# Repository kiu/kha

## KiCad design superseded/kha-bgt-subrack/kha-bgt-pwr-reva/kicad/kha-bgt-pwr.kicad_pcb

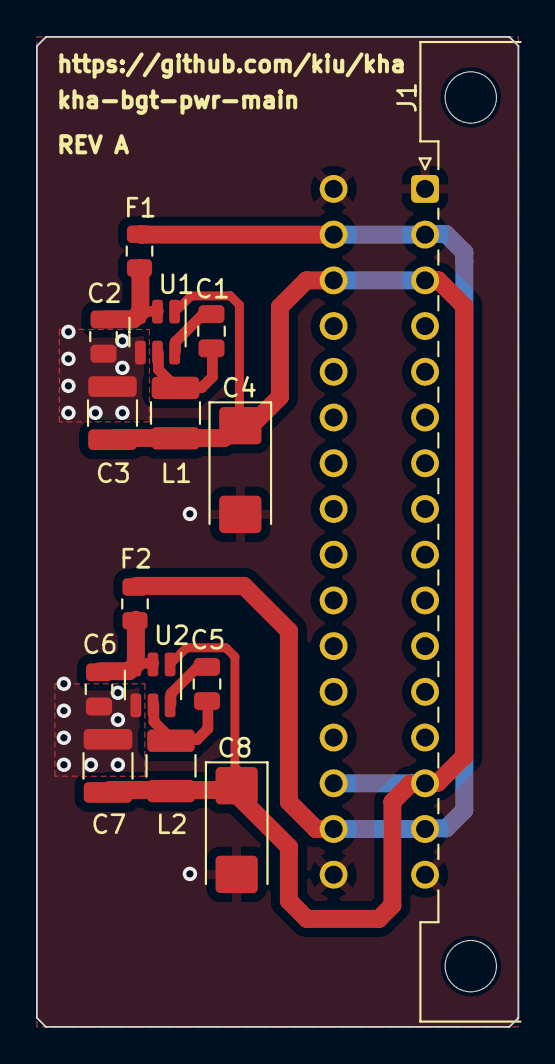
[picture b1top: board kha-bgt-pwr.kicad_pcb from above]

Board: 2 copper layers, 26.8 x 55.0 mm, 15 parts (0 on the bottom side), 9 nets.

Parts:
C1, C2, C5, C6: C; C_0805_2012Metric
C3, C7: C; C_1210_3225Metric
C4, C8: C_Polarized; CP_EIA-6032-28_Kemet-C
F1, F2: Polyfuse; Fuse_0805_2012Metric
J1: DIN41612_02x16_AC; DIN41612_C2_2x16_Male_Horizontal_THT
L1, L2: L; L_1210_3225Metric
U1, U2: AP63205WU; TSOT-23-6

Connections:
+5V: C3.1, C4.1, C7.1, C8.1, J1.a3, J1.a14, J1.c3, J1.c14, L1.2, L2.2, U1.1 (FB), U2.1 (FB)
+12V: F1.2, F2.2, J1.a2, J1.a15, J1.c2, J1.c15
GND: C2.1, C3.2, C4.2, C6.1, C7.2, C8.2, J1.a1, J1.a16, J1.c1, J1.c16, U1.4 (GND), U2.4 (GND)
unnamed: C1.2, U1.6 (BST)
unnamed: C2.2, F1.1, U1.2 (EN), U1.3 (IN)
unnamed: C1.1, L1.1, U1.5 (SW)
unnamed: C5.2, U2.6 (BST)
unnamed: C6.2, F2.1, U2.2 (EN), U2.3 (IN)
unnamed: C5.1, L2.1, U2.5 (SW)

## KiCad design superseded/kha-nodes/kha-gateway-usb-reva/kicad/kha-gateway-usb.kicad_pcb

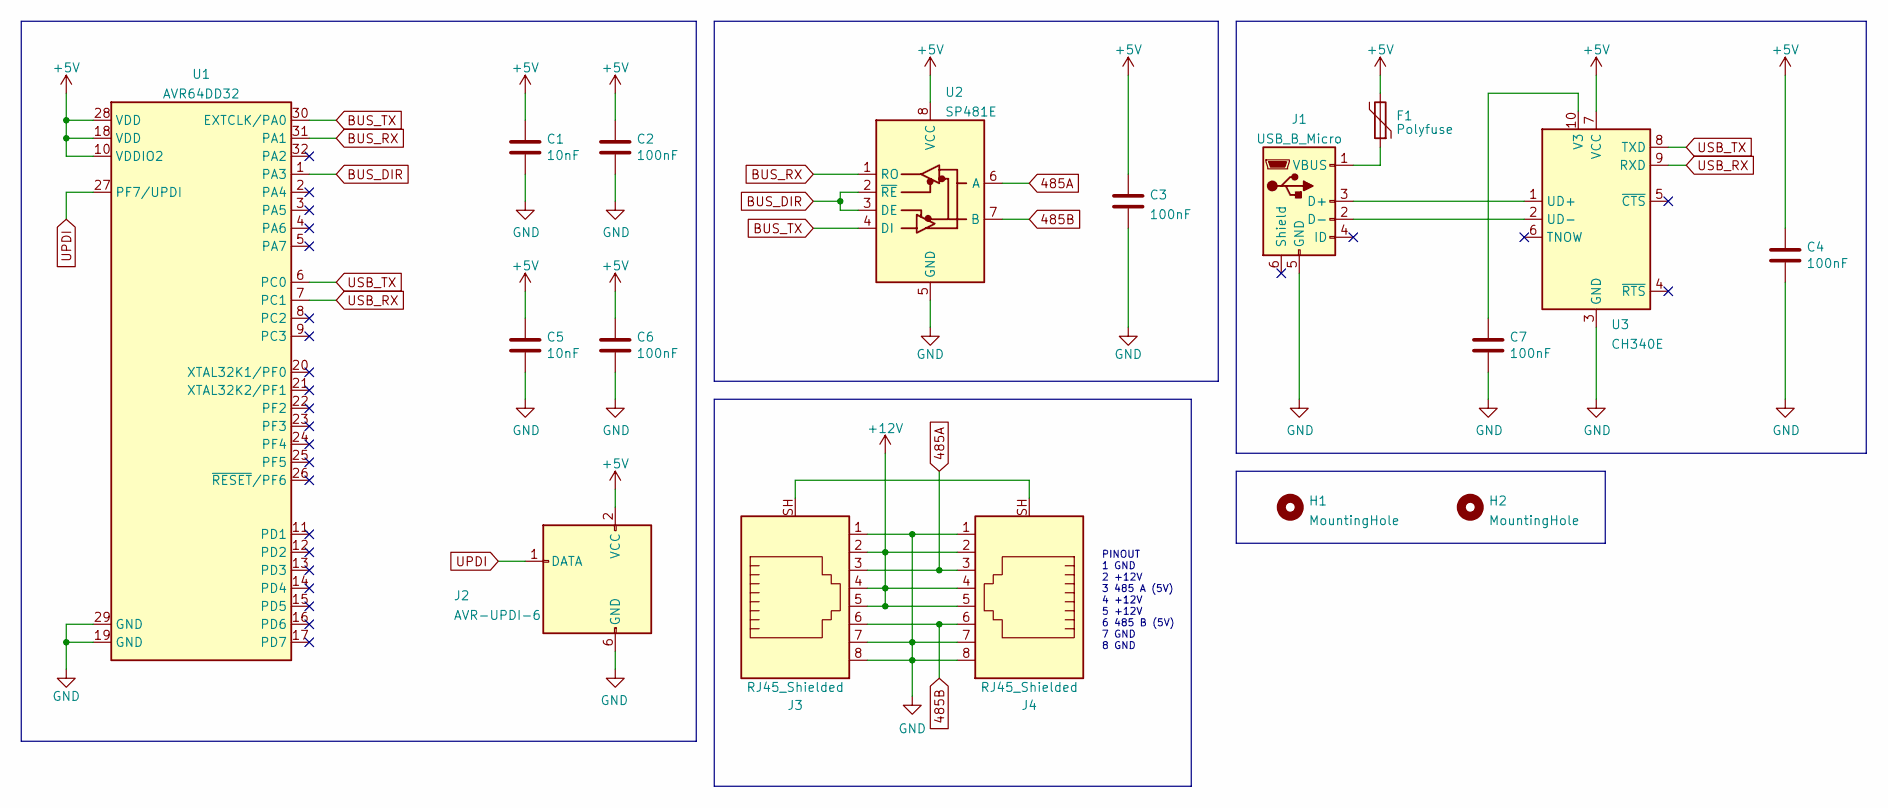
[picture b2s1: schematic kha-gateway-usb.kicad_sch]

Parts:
C1, C5: 10nF; C_0805_2012Metric
C2, C3, C4, C6, C7: 100nF; C_0805_2012Metric
F1: Polyfuse; Fuse_0805_2012Metric
H1, H2: MountingHole; MountingHole_3.2mm_M3_DIN965
J1: USB_B_Micro; GCT-USB3076-30-A
J2: AVR-UPDI-6; eAVR6-UPDI-F
J3, J4: RJ45_Shielded; GDLX-S-88K
U1: AVR64DD32; TQFP-32_7x7mm_P0.8mm
U2: SP481E; SOIC-8_3.9x4.9mm_P1.27mm
U3: CH340E; MSOP-10_3x3mm_P0.5mm

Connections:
485A: J3.3, J4.3, U2.6 (A)
485B: J3.6, J4.6, U2.7 (B)
+5V: C1.1, C2.1, C3.1, C4.1, C5.1, C6.1, F1.2, J2.2 (VCC), U1.10 (VDDIO2), U1.18 (VDD), U1.28 (VDD), U2.8 (VCC), U3.7 (VCC)
+12V: J3.2, J3.4, J3.5, J4.2, J4.4, J4.5
BUS_DIR: U1.1 (PA3), U2.2 (~RE), U2.3 (DE)
BUS_RX: U1.31 (PA1), U2.1 (RO)
BUS_TX: U1.30 (EXTCLK/PA0), U2.4 (DI)
GND: C1.2, C2.2, C3.2, C4.2, C5.2, C6.2, C7.2, J1.5 (GND), J2.6 (GND), J3.1, J3.7, J3.8, J4.1, J4.7, J4.8, U1.19 (GND), U1.29 (GND), U2.5 (GND), U3.3 (GND)
unnamed: J1.3 (D+), U3.1 (UD+)
unnamed: J1.2 (D-), U3.2 (UD-)
unnamed: F1.1, J1.1 (VBUS)
unnamed: J3.SH, J4.SH
unnamed: C7.1, U3.10 (V3)
UPDI: J2.1 (DATA), U1.27 (PF7/UPDI)
USB_RX: U1.7 (PC1), U3.9 (RXD)
USB_TX: U1.6 (PC0), U3.8 (TXD)

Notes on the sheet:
PINOUT 1 GND 2 +12V 3 485 A (5V) 4 +12V 5 +12V 6 485 B (5V) 7 GND 8 GND

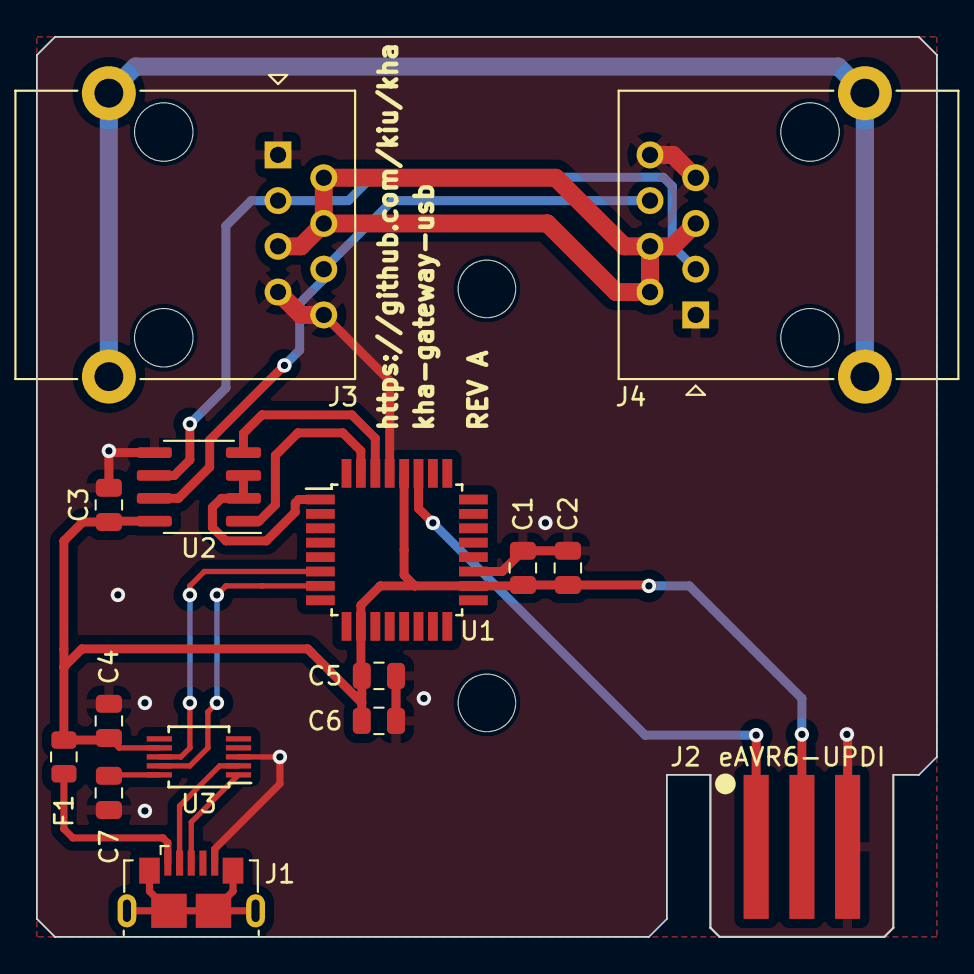
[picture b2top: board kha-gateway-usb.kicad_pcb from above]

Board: 2 copper layers, 50.0 x 50.0 mm, 17 parts (0 on the bottom side), 16 nets.

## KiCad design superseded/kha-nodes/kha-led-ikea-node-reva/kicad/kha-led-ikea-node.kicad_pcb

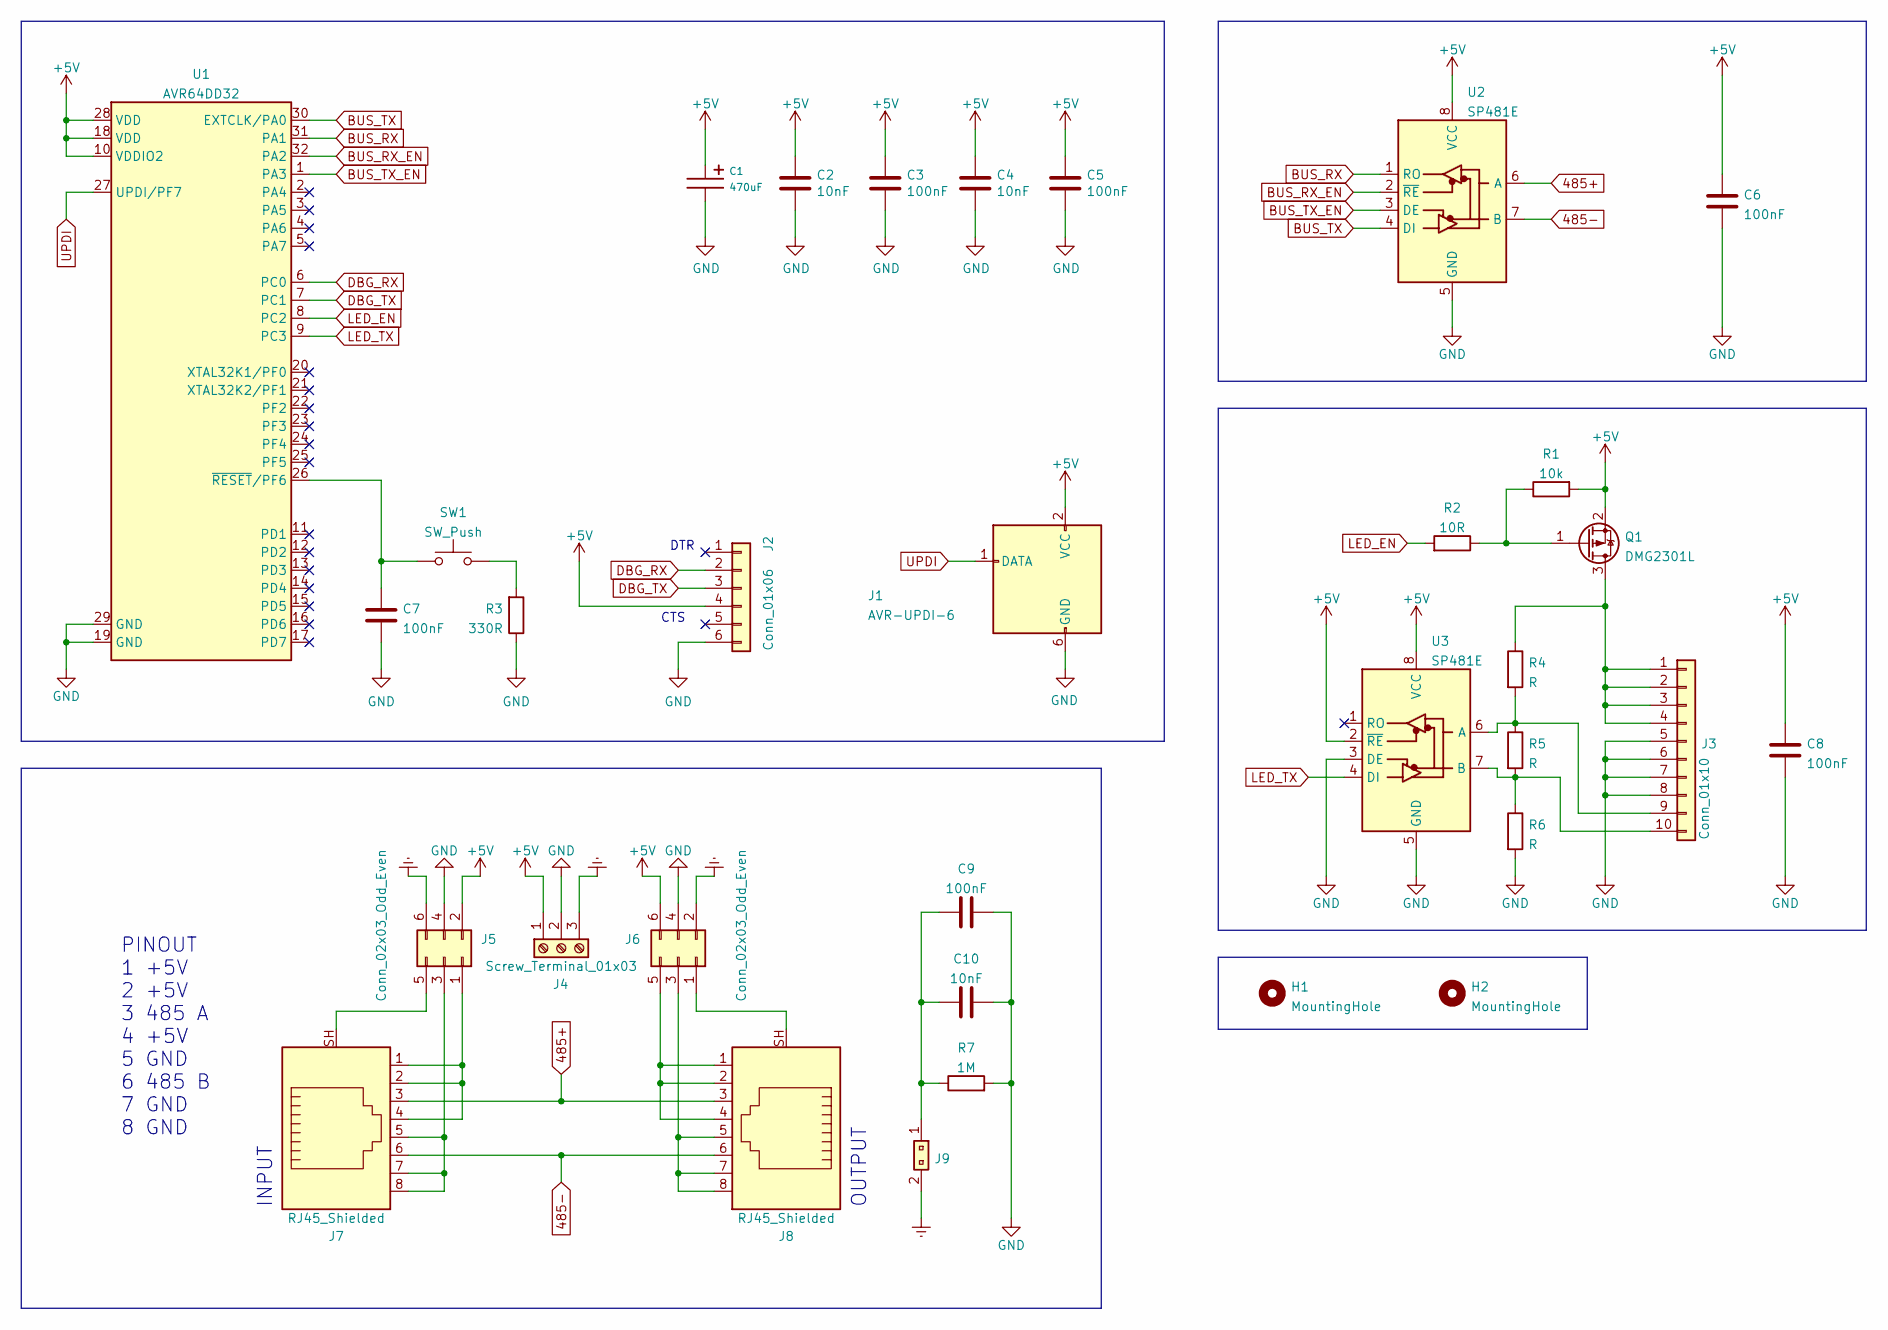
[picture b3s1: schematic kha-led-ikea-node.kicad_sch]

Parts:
C1: 470uF; CP_Elec_8x10
C2, C4, C10: 10nF; C_0805_2012Metric
C3, C5, C6, C7, C8, C9: 100nF; C_0805_2012Metric
H1, H2: MountingHole; MountingHole_3.2mm_M3
J1: AVR-UPDI-6; eAVR6-UPDI-F
J2: Conn_01x06; PinSocket_1x06_P2.54mm_Vertical
J3: Conn_01x10; IDC-Header_2x05_P2.54mm_Vertical
J4: Screw_Terminal_01x03; TerminalBlock_RND_205-00233_1x03_P5.08mm_Horizontal
J5, J6: Conn_02x03_Odd_Even; PinHeader_2x03_P2.54mm_Vertical
J7, J8: RJ45_Shielded; GDLX-S-88K
J9: 1x02_Jumper; PinHeader_1x02_P2.54mm_Vertical
Q1: DMG2301L; SOT-23
R1: 10k; R_0805_2012Metric
R2: 10R; R_0805_2012Metric
R3: 330R; R_0805_2012Metric
R4, R5, R6: R; R_0805_2012Metric
R7: 1M; R_0805_2012Metric
SW1: SW_Push; SW_Push_1P1T_NO_6x6mm_H9.5mm
U1: AVR64DD32; TQFP-32_7x7mm_P0.8mm
U2, U3: SP481E; SOIC-8_3.9x4.9mm_P1.27mm

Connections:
485+: J7.3, J8.3, U2.6 (A)
485-: J7.6, J8.6, U2.7 (B)
+5V: C1.1, C2.1, C3.1, C4.1, C5.1, C6.1, C8.1, J1.2 (VCC), J2.4, J4.1, J5.2, J6.6, Q1.2 (S), R1.2, U1.10 (VDDIO2), U1.18 (VDD), U1.28 (VDD), U2.8 (VCC), U3.2 (~RE), U3.8 (VCC)
BUS_RX: U1.31 (PA1), U2.1 (RO)
BUS_RX_EN: U1.32 (PA2), U2.2 (~RE)
BUS_TX: U1.30 (EXTCLK/PA0), U2.4 (DI)
BUS_TX_EN: U1.1 (PA3), U2.3 (DE)
DBG_RX: J2.2, U1.6 (PC0)
DBG_TX: J2.3, U1.7 (PC1)
Earth: J4.3, J5.6, J6.2, J9.2
GND: C1.2, C2.2, C3.2, C4.2, C5.2, C6.2, C7.2, C8.2, C9.2, C10.2, J1.6 (GND), J2.6, J3.5, J3.6, J3.7, J3.8, J4.2, J5.4, J6.4, R3.1, R6.2, R7.2, U1.19 (GND), U1.29 (GND), U2.5 (GND), U3.3 (DE), U3.5 (GND)
LED_EN: R2.2, U1.8 (PC2)
LED_TX: U1.9 (PC3), U3.4 (DI)
unnamed: C7.1, SW1.1, U1.26 (~RESET/PF6)
unnamed: C9.1, C10.1, J9.1, R7.1
unnamed: J3.1, J3.2, J3.3, J3.4, Q1.3 (D), R4.1
unnamed: J3.9, R4.2, R5.1, U3.6 (A)
unnamed: J5.1, J7.1, J7.2, J7.4
unnamed: J5.3, J7.5, J7.7, J7.8
unnamed: J5.5, J7.SH
unnamed: J6.1, J8.SH
unnamed: J6.3, J8.5, J8.7, J8.8
unnamed: J6.5, J8.1, J8.2, J8.4
unnamed: Q1.1 (G), R1.1, R2.1
unnamed: R3.2, SW1.2
unnamed: J3.10, R5.2, R6.1, U3.7 (B)
UPDI: J1.1 (DATA), U1.27 (UPDI/PF7)

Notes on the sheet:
CTS
PINOUT 1 +5V 2 +5V 3 485 A 4 +5V 5 GND 6 485 B 7 GND 8 GND
OUTPUT
INPUT
DTR

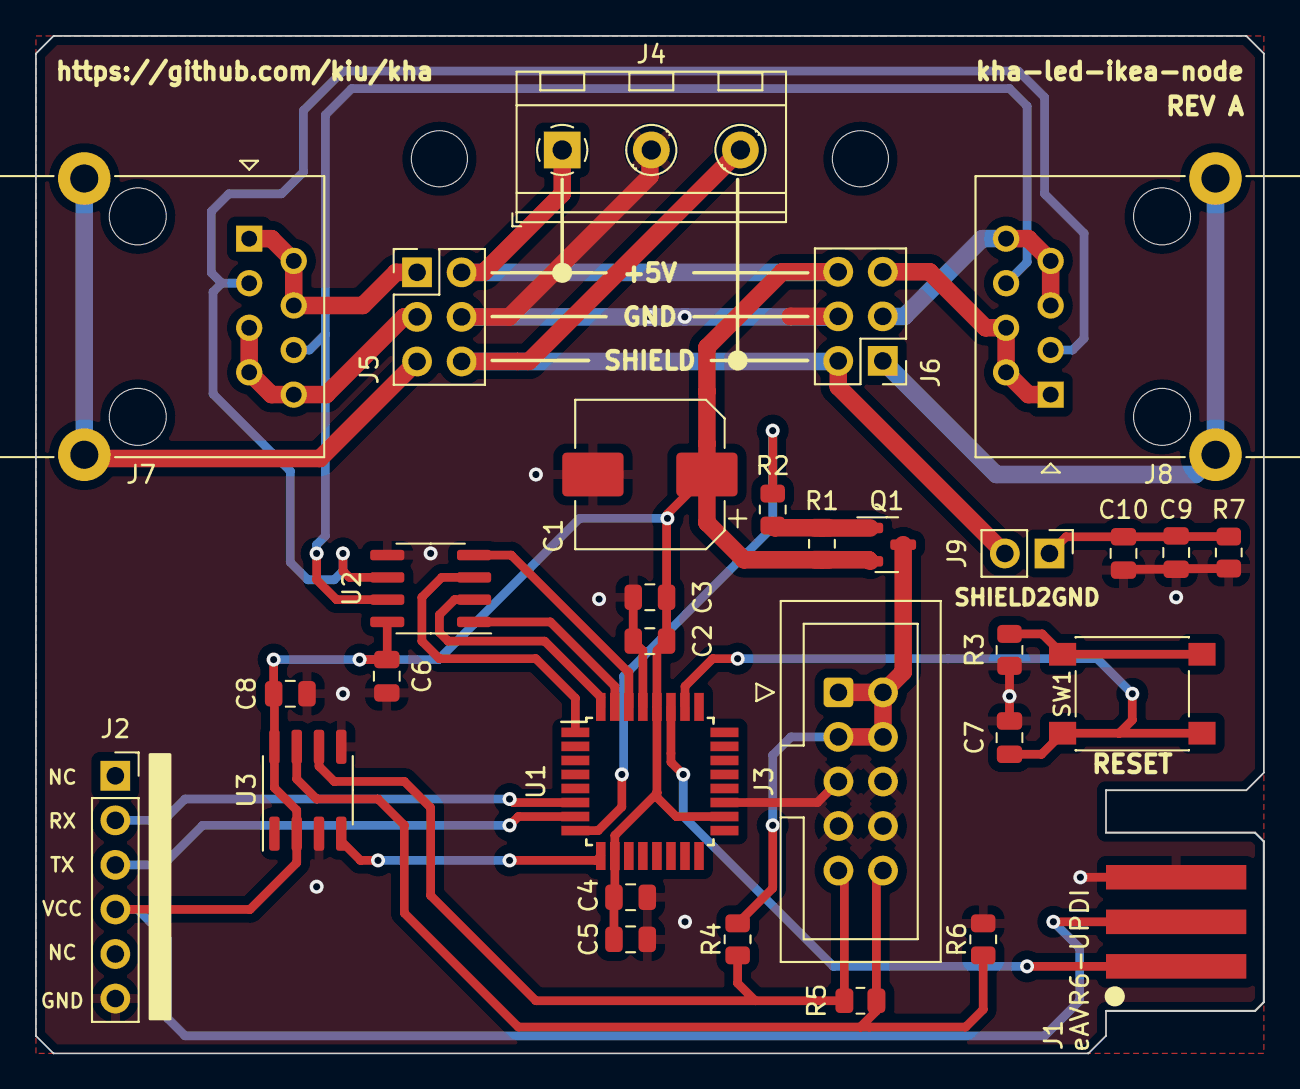
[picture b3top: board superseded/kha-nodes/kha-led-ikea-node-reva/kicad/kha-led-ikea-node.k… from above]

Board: 2 copper layers, 70.0 x 58.0 mm, 33 parts (0 on the bottom side), 27 nets.

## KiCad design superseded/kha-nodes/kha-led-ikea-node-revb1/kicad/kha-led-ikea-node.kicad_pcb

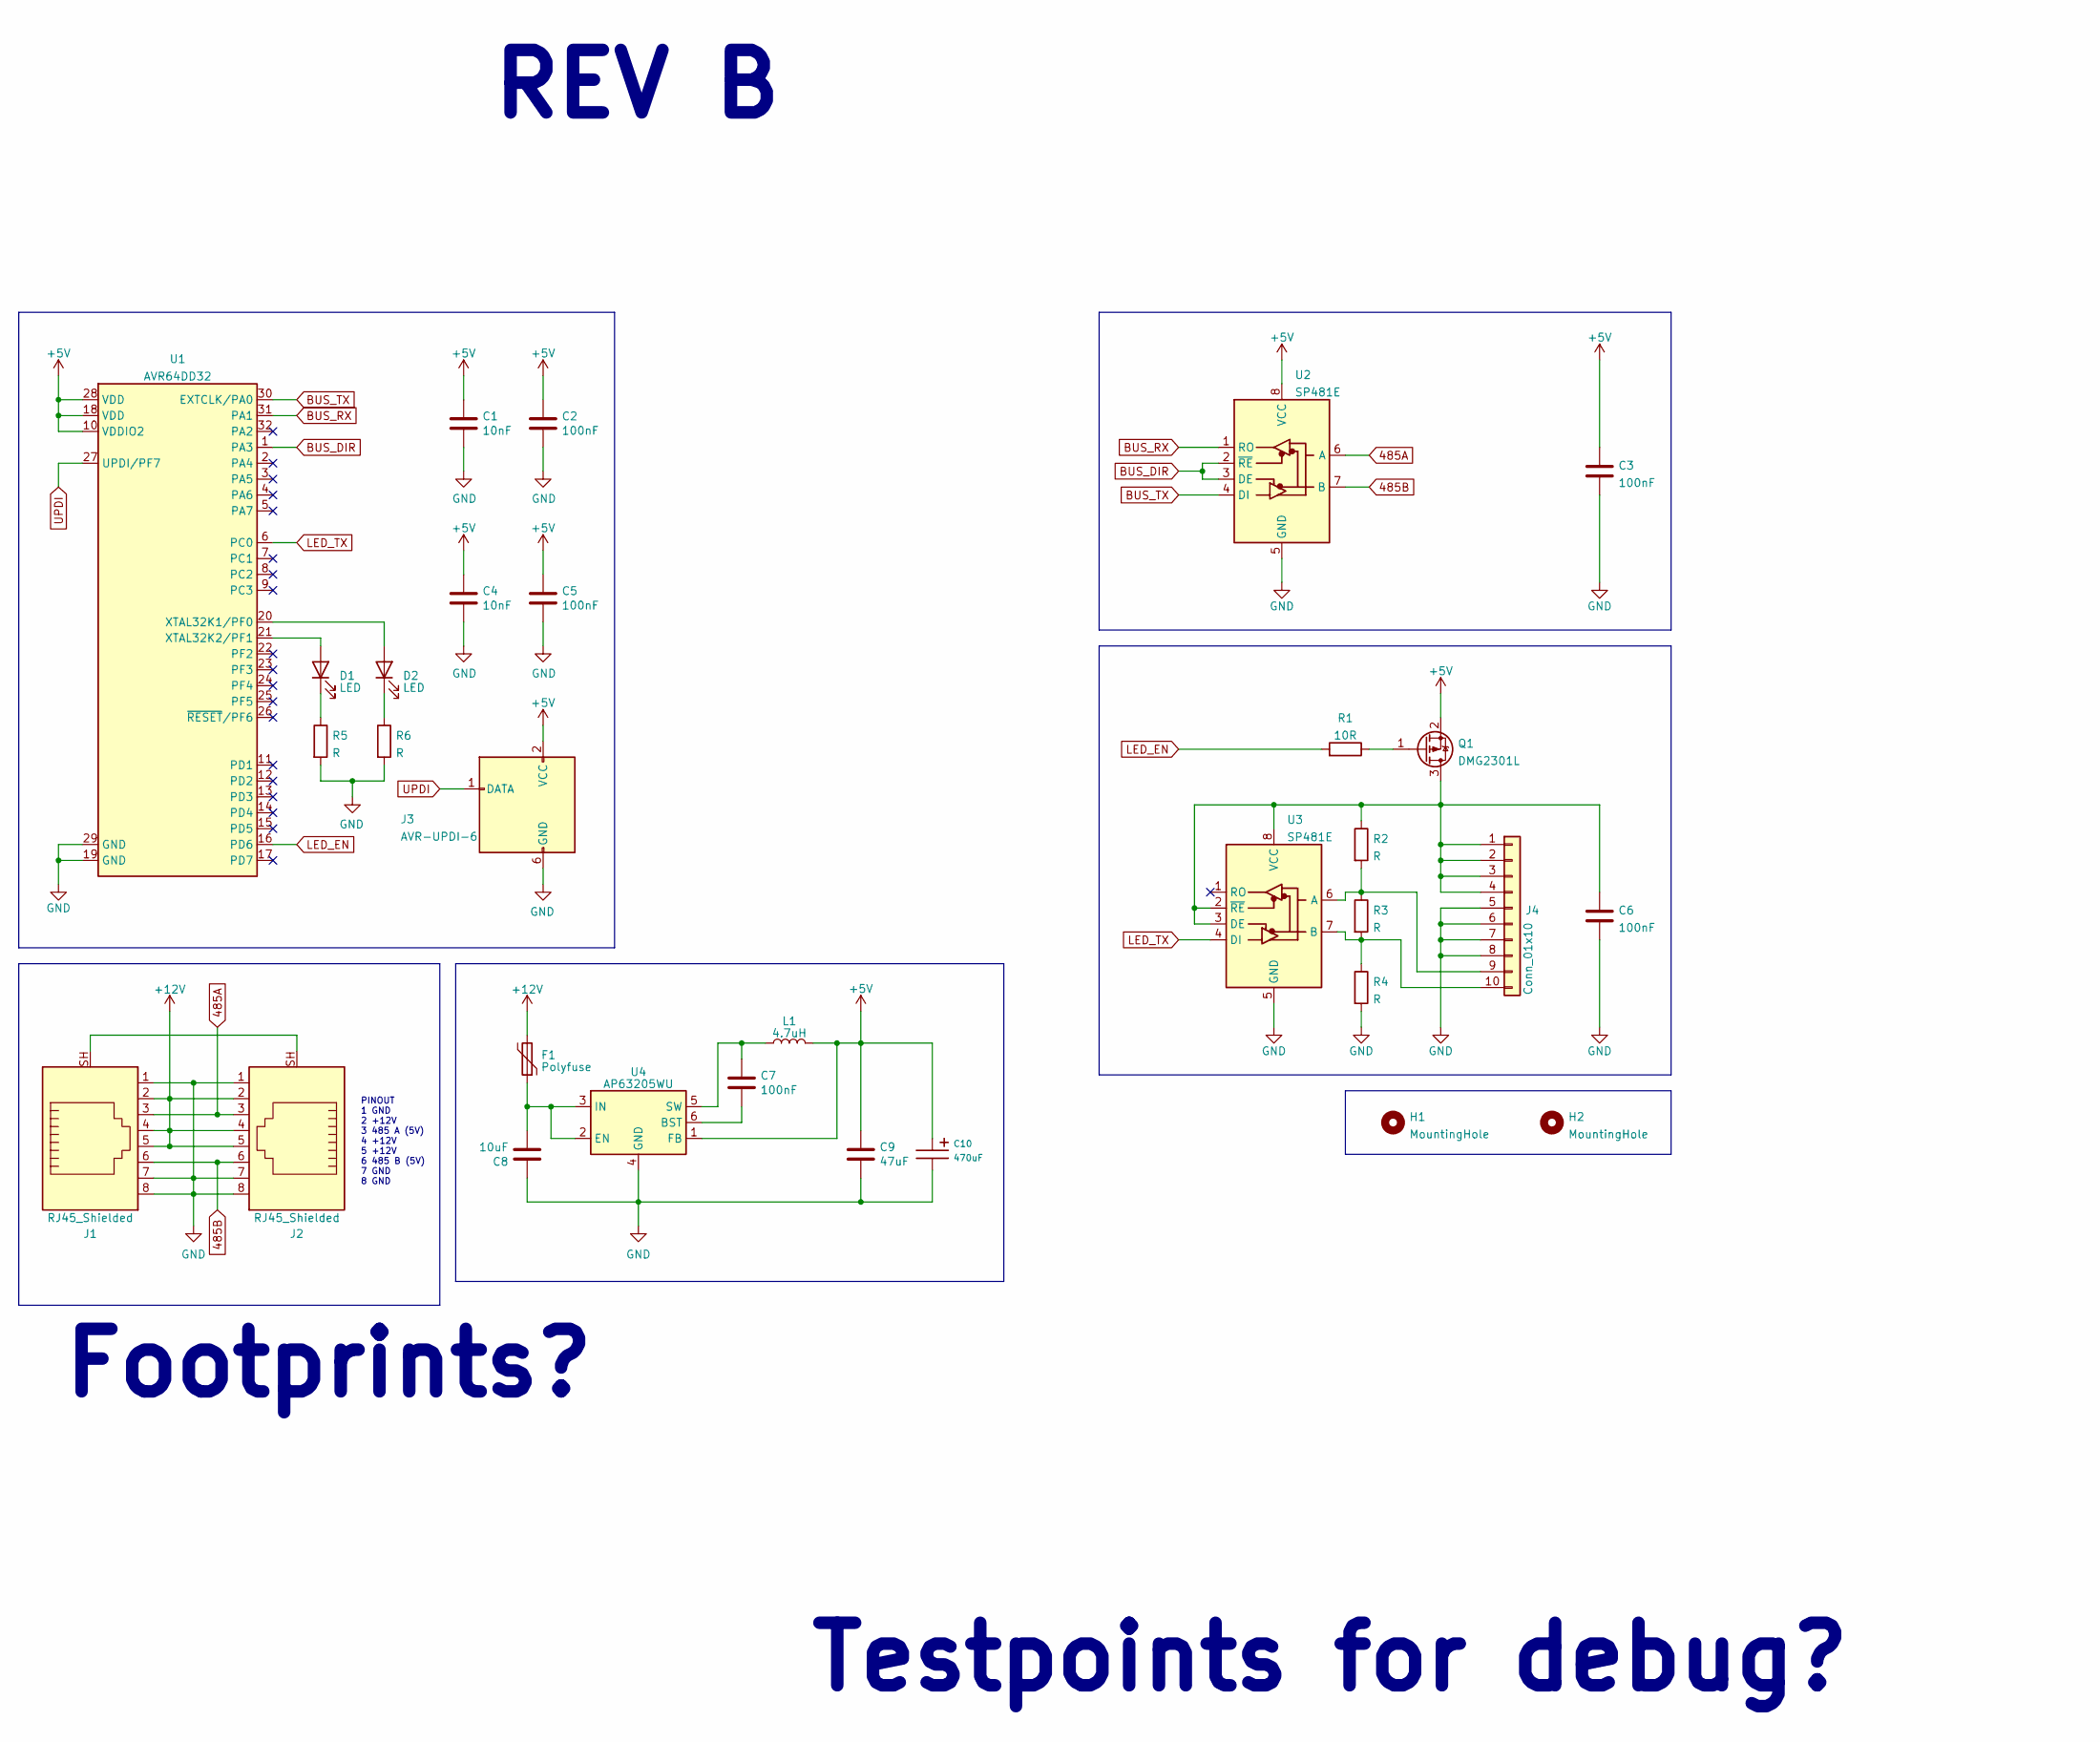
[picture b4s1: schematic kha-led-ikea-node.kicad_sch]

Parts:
C1: 10nF; L_0805_2012Metric
C2, C3, C5, C6, C7: 100nF; C_0805_2012Metric
C4: 10nF; C_0805_2012Metric
C8: 10uF; C_0805_2012Metric
C9: 47uF; C_1210_3225Metric
C10: 470uF; CP_Elec_8x10
D1, D2: LED; LED_0805_2012Metric
F1: Polyfuse; Fuse_1206_3216Metric
H1, H2: MountingHole; MountingHole_3.2mm_M3_DIN965
J1, J2: RJ45_Shielded; GDLX-S-88K
J3: AVR-UPDI-6; eAVR6-UPDI-F
J4: Conn_01x10; IDC-Header_2x05_P2.54mm_Vertical
L1: 4.7uH; L_6.3x6.3_H3
Q1: DMG2301L; SOT-23
R1: 10R; R_0805_2012Metric
R2, R3, R4, R5, R6: R; R_0805_2012Metric
U1: AVR64DD32; TQFP-32_7x7mm_P0.8mm
U2, U3: SP481E; SOIC-8_3.9x4.9mm_P1.27mm
U4: AP63205WU; TSOT-23-6

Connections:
485A: J1.3, J2.3, U2.6 (A)
485B: J1.6, J2.6, U2.7 (B)
+5V: C1.1, C2.1, C3.1, C4.1, C5.1, C9.1, C10.1, J3.2 (VCC), L1.2, Q1.2 (S), U1.10 (VDDIO2), U1.18 (VDD), U1.28 (VDD), U2.8 (VCC), U4.1 (FB)
+12V: F1.2, J1.2, J1.4, J1.5, J2.2, J2.4, J2.5
BUS_DIR: U1.1 (PA3), U2.2 (~RE), U2.3 (DE)
BUS_RX: U1.31 (PA1), U2.1 (RO)
BUS_TX: U1.30 (EXTCLK/PA0), U2.4 (DI)
GND: C1.2, C2.2, C3.2, C4.2, C5.2, C6.2, C8.1, C9.2, C10.2, J1.1, J1.7, J1.8, J2.1, J2.7, J2.8, J3.6 (GND), J4.5, J4.6, J4.7, J4.8, R4.2, R5.2, R6.2, U1.19 (GND), U1.29 (GND), U2.5 (GND), U3.5 (GND), U4.4 (GND)
LED_EN: R1.2, U1.16 (PD6)
LED_TX: U1.6 (PC0), U3.4 (DI)
unnamed: D1.2 (A), U1.21 (XTAL32K2/PF1)
unnamed: D1.1 (K), R5.1
unnamed: D2.2 (A), U1.20 (XTAL32K1/PF0)
unnamed: D2.1 (K), R6.1
unnamed: J1.SH, J2.SH
unnamed: C6.1, J4.1, J4.2, J4.3, J4.4, Q1.3 (D), R2.1, U3.2 (~RE), U3.3 (DE), U3.8 (VCC)
unnamed: J4.9, R2.2, R3.1, U3.6 (A)
unnamed: J4.10, R3.2, R4.1, U3.7 (B)
unnamed: Q1.1 (G), R1.1
unnamed: C7.2, U4.6 (BST)
unnamed: C8.2, F1.1, U4.2 (EN), U4.3 (IN)
unnamed: C7.1, L1.1, U4.5 (SW)
UPDI: J3.1 (DATA), U1.27 (UPDI/PF7)

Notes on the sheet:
REV B
Testpoints for debug?
PINOUT 1 GND 2 +12V 3 485 A (5V) 4 +12V 5 +12V 6 485 B (5V) 7 GND 8 GND
Footprints?

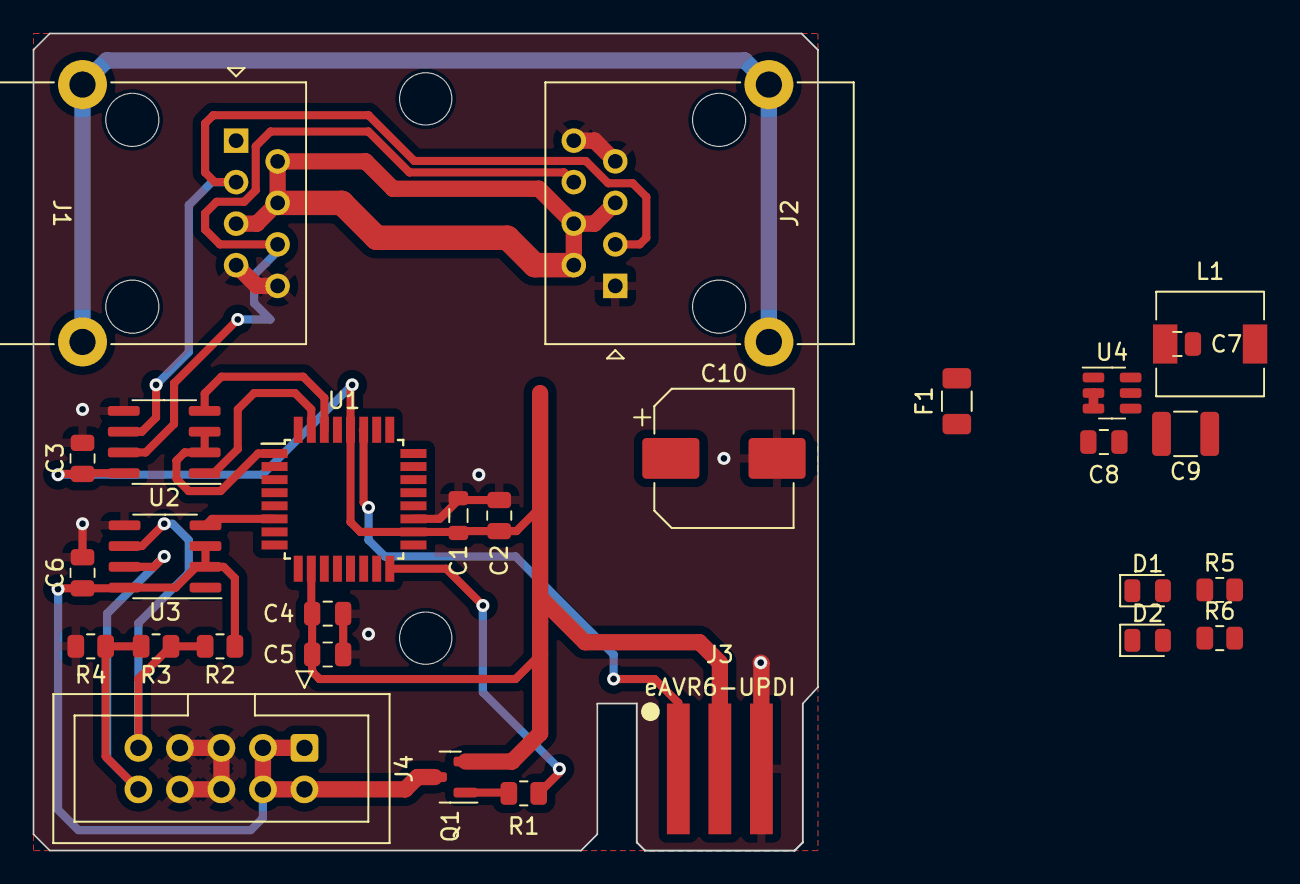
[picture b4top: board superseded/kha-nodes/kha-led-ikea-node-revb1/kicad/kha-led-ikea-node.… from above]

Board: 2 copper layers, 48.0 x 50.0 mm, 31 parts (0 on the bottom side), 23 nets.

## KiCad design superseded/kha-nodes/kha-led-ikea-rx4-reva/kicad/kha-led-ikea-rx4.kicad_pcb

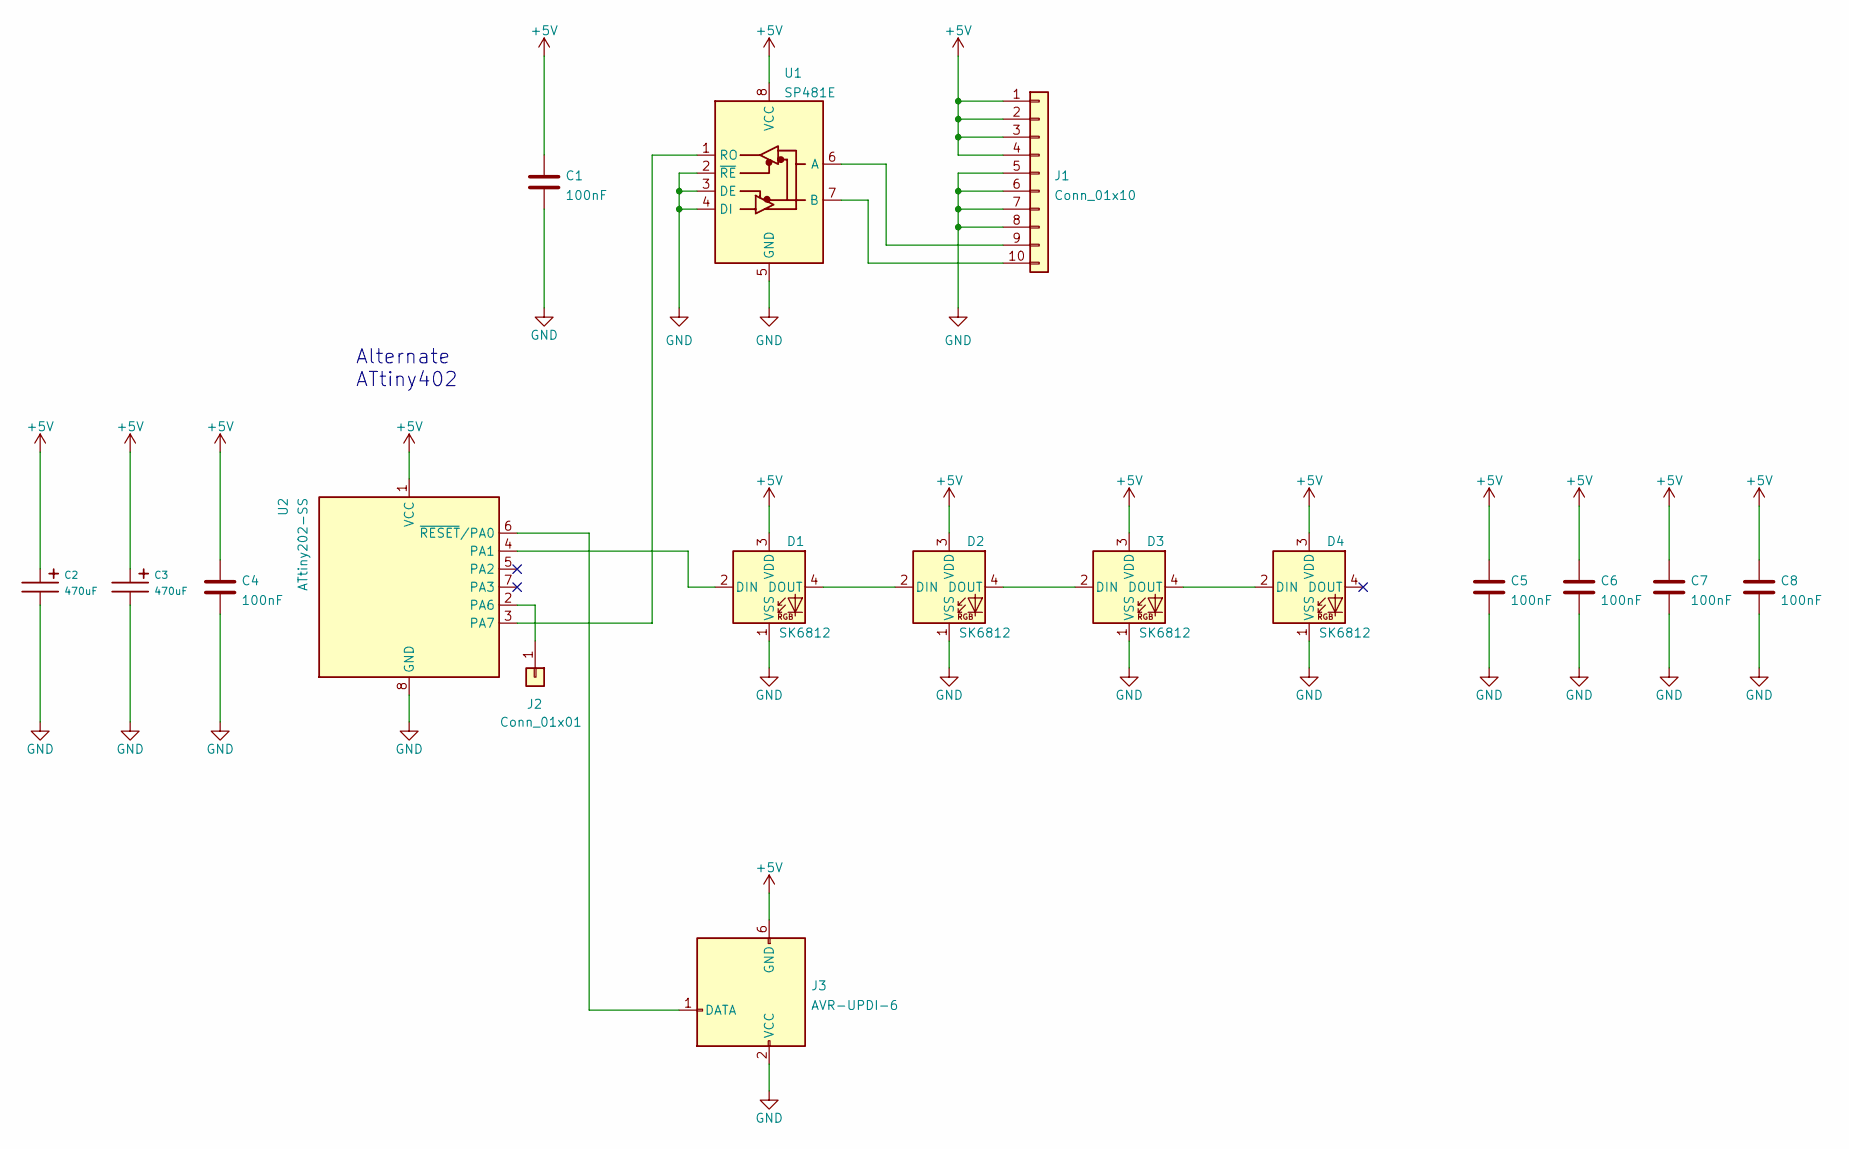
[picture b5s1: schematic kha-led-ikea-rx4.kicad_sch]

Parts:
C1, C4, C5, C6, C7, C8: 100nF; C_0805_2012Metric
C2, C3: 470uF; CP_EIA-6032-28_Kemet-C
D1, D2, D3, D4: SK6812; LED_SK6812_PLCC4_5.0x5.0mm_P3.2mm
J1: Conn_01x10; IDC-Header_2x05_P2.54mm_Vertical
J2: Conn_01x01; TestPoint_Pad_1.5x1.5mm
J3: AVR-UPDI-6; eAVR6-UPDI-F
U1: SP481E; SOIC-8_3.9x4.9mm_P1.27mm
U2: ATtiny202-SS; SOIC-8_3.9x4.9mm_P1.27mm

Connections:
+5V: C1.1, C2.1, C3.1, C4.1, C5.1, C6.1, C7.1, C8.1, D1.3 (VDD), D2.3 (VDD), D3.3 (VDD), D4.3 (VDD), J1.1, J1.2, J1.3, J1.4, J3.6 (GND), U1.8 (VCC), U2.1 (VCC)
GND: C1.2, C2.2, C3.2, C4.2, C5.2, C6.2, C7.2, C8.2, D1.1 (VSS), D2.1 (VSS), D3.1 (VSS), D4.1 (VSS), J1.5, J1.6, J1.7, J1.8, J3.2 (VCC), U1.2 (~RE), U1.3 (DE), U1.4 (DI), U1.5 (GND), U2.8 (GND)
unnamed: D1.2 (DIN), U2.4 (PA1)
unnamed: D1.4 (DOUT), D2.2 (DIN)
unnamed: D2.4 (DOUT), D3.2 (DIN)
unnamed: D3.4 (DOUT), D4.2 (DIN)
unnamed: J1.9, U1.6 (A)
unnamed: J1.10, U1.7 (B)
unnamed: J2.1, U2.2 (PA6)
unnamed: J3.1 (DATA), U2.6 (~RESET/PA0)
unnamed: U1.1 (RO), U2.3 (PA7)

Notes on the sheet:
Alternate ATtiny402

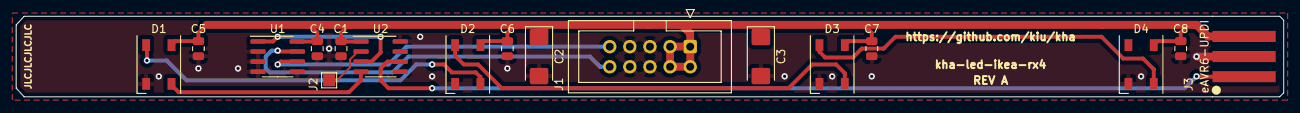
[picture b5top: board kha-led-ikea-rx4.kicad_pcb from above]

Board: 2 copper layers, 160.0 x 10.2 mm, 17 parts (0 on the bottom side), 11 nets.
